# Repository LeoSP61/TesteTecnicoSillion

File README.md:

# TesteTecnicoSillion
Desafio Hardware/Firmware - Sillion

Considerações iniciais: 
O Projeto foi feito seguindo as premissas apresentadas no documento Desafio Hardware/Firmware - Sillion (https://docs.google.com/document/d/1DJPGadSPsPmk1VQU9ZT9On-CVbZ3AcXDxckCV0j4miA/edit).

Como não foram especificadas as características do motor, assumi todo o circuito não consumiria mais que 2A. 

Devido ao prazo curto, não desenvolvi por completo a fonte opcional do exercício 6. Porém, tenho o costume de dimensionar fontes/conversores utilizando a ferramenta WEBENCH POWER DESIGNER da Texas Instruments como auxílio. 
Então entrei com as características necessárias: Conversor Buck (ou buck_boost) entrada 5V a 36V e saída 5V@2A. A partir dos resultados escolhi o circuito que utiliza o CI TPS55288RPMR por ter um footprint reduzido e disponibilidade no mercado. 
O relatório do circuito modelo está anexado no repositório.

Qualquer dúvida, sintam-se a vontade para entrar em contato.

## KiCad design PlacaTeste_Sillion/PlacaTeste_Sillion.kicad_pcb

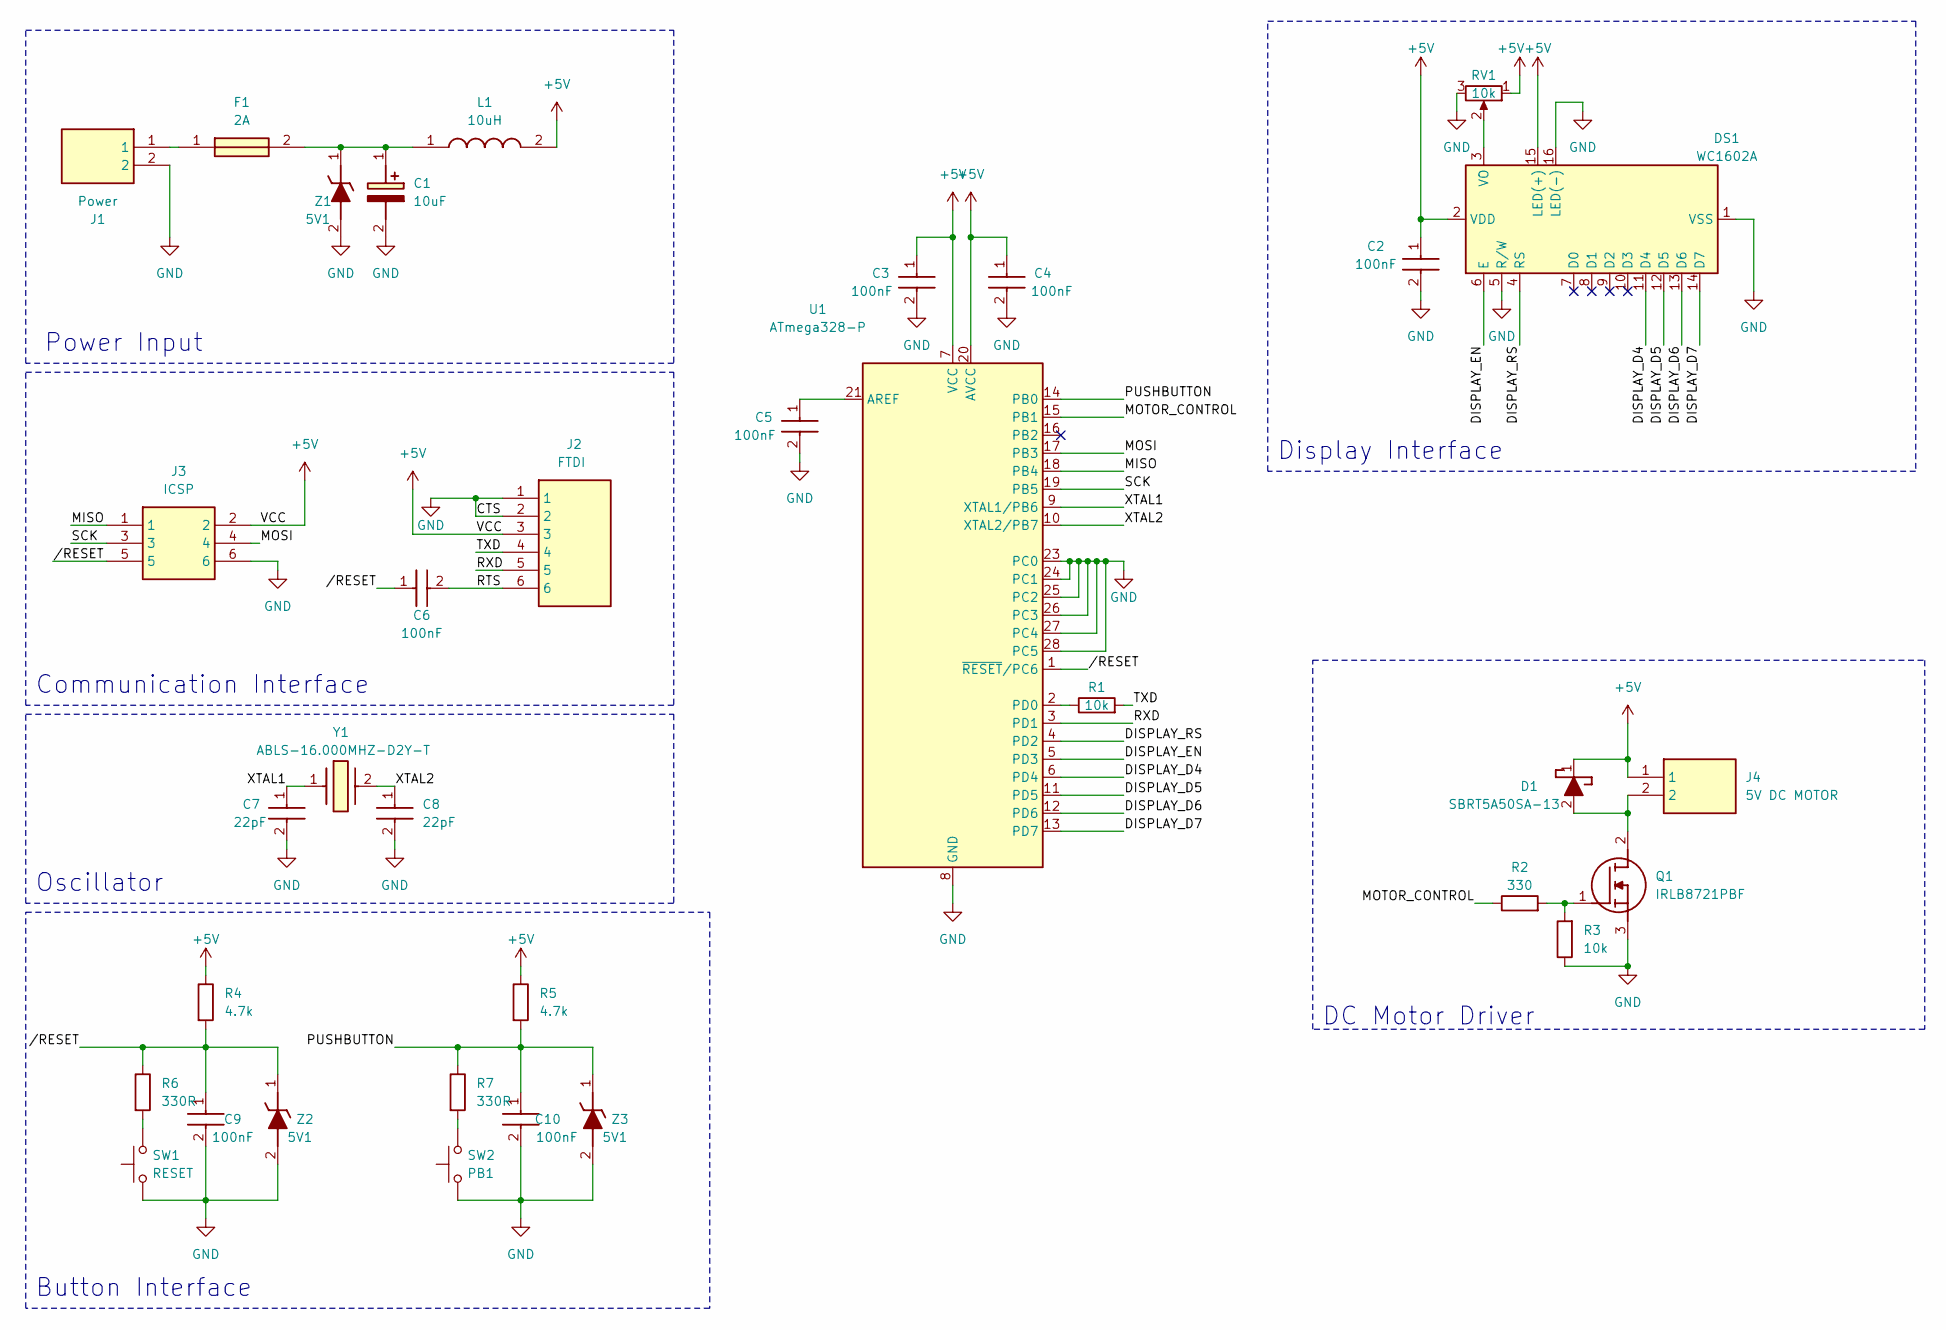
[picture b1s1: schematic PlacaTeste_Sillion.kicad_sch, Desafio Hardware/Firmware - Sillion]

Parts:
C1: 10uF; EEE1AA220WR; Mouser Part Number 667-EEE-FTH100UAR
C2, C3, C4, C5, C6, C9, C10: 100nF; CAPC2012X145N; Mouser Part Number 77-VJ0805Y104MXAMR
C7, C8: 22pF; CAPC2012X94N; Mouser Part Number 581-08055A220FAT2A
D1: SBRT5A50SA-13; DIOM5226X240N; Mouser Part Number 621-SBRT5A50SA-13
DS1: WC1602A
F1: 2A; 39512000000; Mouser Part Number 576-3951200000
J1: Power; 1731721; Mouser Part Number 651-1731721
J2: FTDI; HDRV6W64P0X254_1X6_1524X254X838P; Mouser Part Number 200-HTSW10607TS
J3: ICSP; HDRV6W64P254_2X3_762X508X838P; Manufacturer_Part_Number TSW-103-23-T-D
J4: 5V DC MOTOR; 1731721; Mouser Part Number 651-1731721
L1: 10uH; INDPM4441X120N; Mouser Part Number 652-SRP4012CC-3R3M
Q1: IRLB8721PBF; TO254P483X1016X1994-3P; Mouser Part Number 942-IRLB8721PBF
R1, R3: 10k; R_0805_2012Metric; Manufacturer_Part_Number RP0805BRD0710KL; Mouser Part Number 603-RP0805BRD0710KL
R2: 330; R_0805_2012Metric; Manufacturer_Part_Number SDR10EZPJ331; Mouser Part Number 755-SDR10EZPJ331
R4, R5: 4.7k; R_0805_2012Metric; Manufacturer_Part_Number ERJ-HP6D4701V; Mouser Part Number 667-ERJ-HP6D4701V
R6, R7: 330R; R_0805_2012Metric; Manufacturer_Part_Number SDR10EZPJ331; Mouser Part Number 755-SDR10EZPJ331
RV1: 10k; PVG5A100C03R00; Manufacturer_Part_Number PVG5A100C03R00; Mouser Part Number 81-PVG5A100C03R00
SW1: RESET; TS026643BK260LCRD; Manufacture_Part_Number TS02-66-43-BK-260-LCR-D; Mouser Part Number 179-TS026643BK260LCR
SW2: PB1; TS026643BK260LCRD; Manufacture_Part_Number TS02-66-43-BK-260-LCR-D; Mouser Part Number 179-TS026643BK260LCR
U1: ATmega328-P; DIP-28_W7.62mm; Manufacturer_Part_Number ATMEGA328P-PN; Mouser Part Number 556-ATMEGA328P-PN
Y1: ABLS-16.000MHZ-D2Y-T; ABLS; Mouser Part Number 815-ABLS16MHZD2YT
Z1, Z2, Z3: 5V1; PTZTFTE2551B; Mouser Part Number 755-PTZTFTE255.1B

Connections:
+5V: C2.1, C3.1, C4.1, D1.1 (K), DS1.2 (VDD), DS1.15 (LED(+)), J2.3, J3.2, J4.1, L1.2, R4.1, R5.1, RV1.1, U1.7 (VCC), U1.20 (AVCC)
/DISPLAY_D4: DS1.11 (D4), U1.6 (PD4)
/DISPLAY_D5: DS1.12 (D5), U1.11 (PD5)
/DISPLAY_D6: DS1.13 (D6), U1.12 (PD6)
/DISPLAY_D7: DS1.14 (D7), U1.13 (PD7)
/DISPLAY_EN: DS1.6 (E), U1.5 (PD3)
/DISPLAY_RS: DS1.4 (RS), U1.4 (PD2)
/MISO: J3.1, U1.18 (PB4)
/MOSI: J3.4, U1.17 (PB3)
/MOTOR_CONTROL: R2.1, U1.15 (PB1)
/PUSHBUTTON: C10.1, R5.2, R7.1, U1.14 (PB0), Z3.1 (K)
/RTS: C6.2, J2.6
/RXD: J2.5, U1.3 (PD1)
/SCK: J3.3, U1.19 (PB5)
/TXD: J2.4, R1.2
/XTAL1: C7.1, U1.9 (XTAL1/PB6), Y1.1
/XTAL2: C8.1, U1.10 (XTAL2/PB7), Y1.2
//RESET: C6.1, C9.1, J3.5, R4.2, R6.1, U1.1 (~RESET/PC6), Z2.1 (K)
GND: C1.2 (-), C2.2, C3.2, C4.2, C5.2, C7.2, C8.2, C9.2, C10.2, DS1.1 (VSS), DS1.5 (R/W), DS1.16 (LED(-)), J1.2, J2.1, J2.2, J3.6, Q1.3 (S), R3.1, RV1.3, SW1.1, SW1.2, SW2.1, SW2.2, U1.8 (GND), U1.22 (GND), U1.23 (PC0), U1.24 (PC1), U1.25 (PC2), U1.26 (PC3), U1.27 (PC4), U1.28 (PC5), Z1.2 (A), Z2.2 (A), Z3.2 (A)
unnamed: C1.1 (+), F1.2, L1.1, Z1.1 (K)
unnamed: D1.2 (A), J4.2, Q1.2 (D)
unnamed: DS1.3 (VO), RV1.2
unnamed: F1.1, J1.1
unnamed: Q1.1 (G), R2.2, R3.2
unnamed: R6.2, SW1.3, SW1.4
unnamed: R7.2, SW2.3, SW2.4
unnamed: C5.1, U1.21 (AREF)
unnamed: R1.1, U1.2 (PD0)

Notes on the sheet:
Display Interface
Oscillator
DC Motor Driver
Communication Interface
Button Interface
Power Input

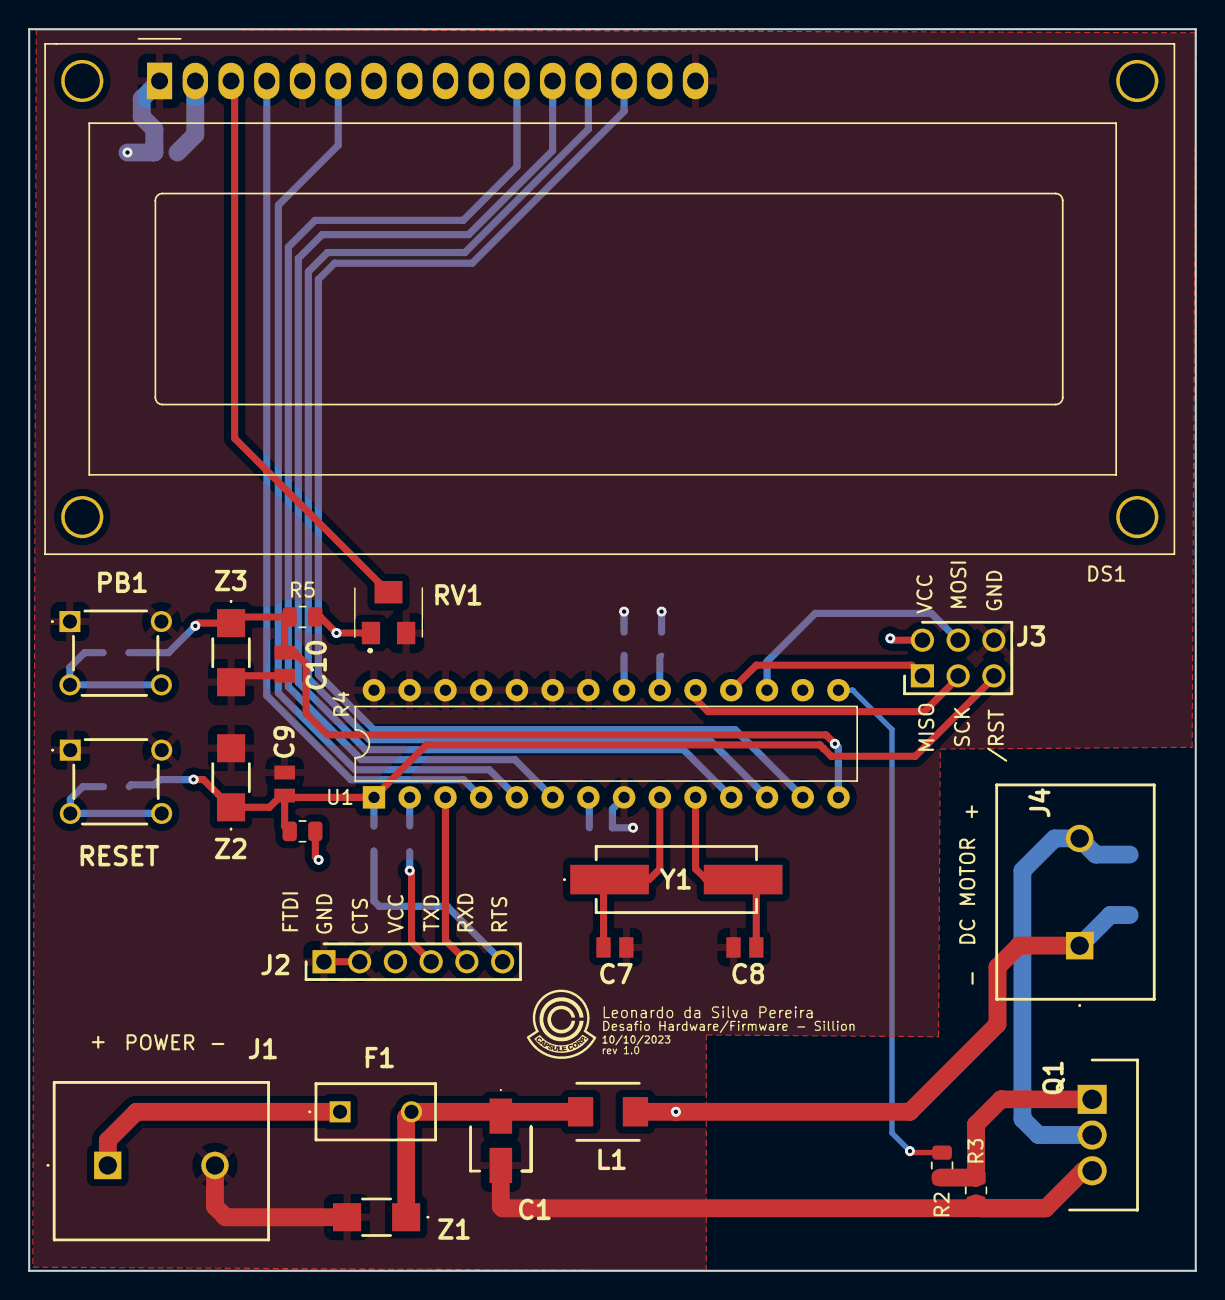
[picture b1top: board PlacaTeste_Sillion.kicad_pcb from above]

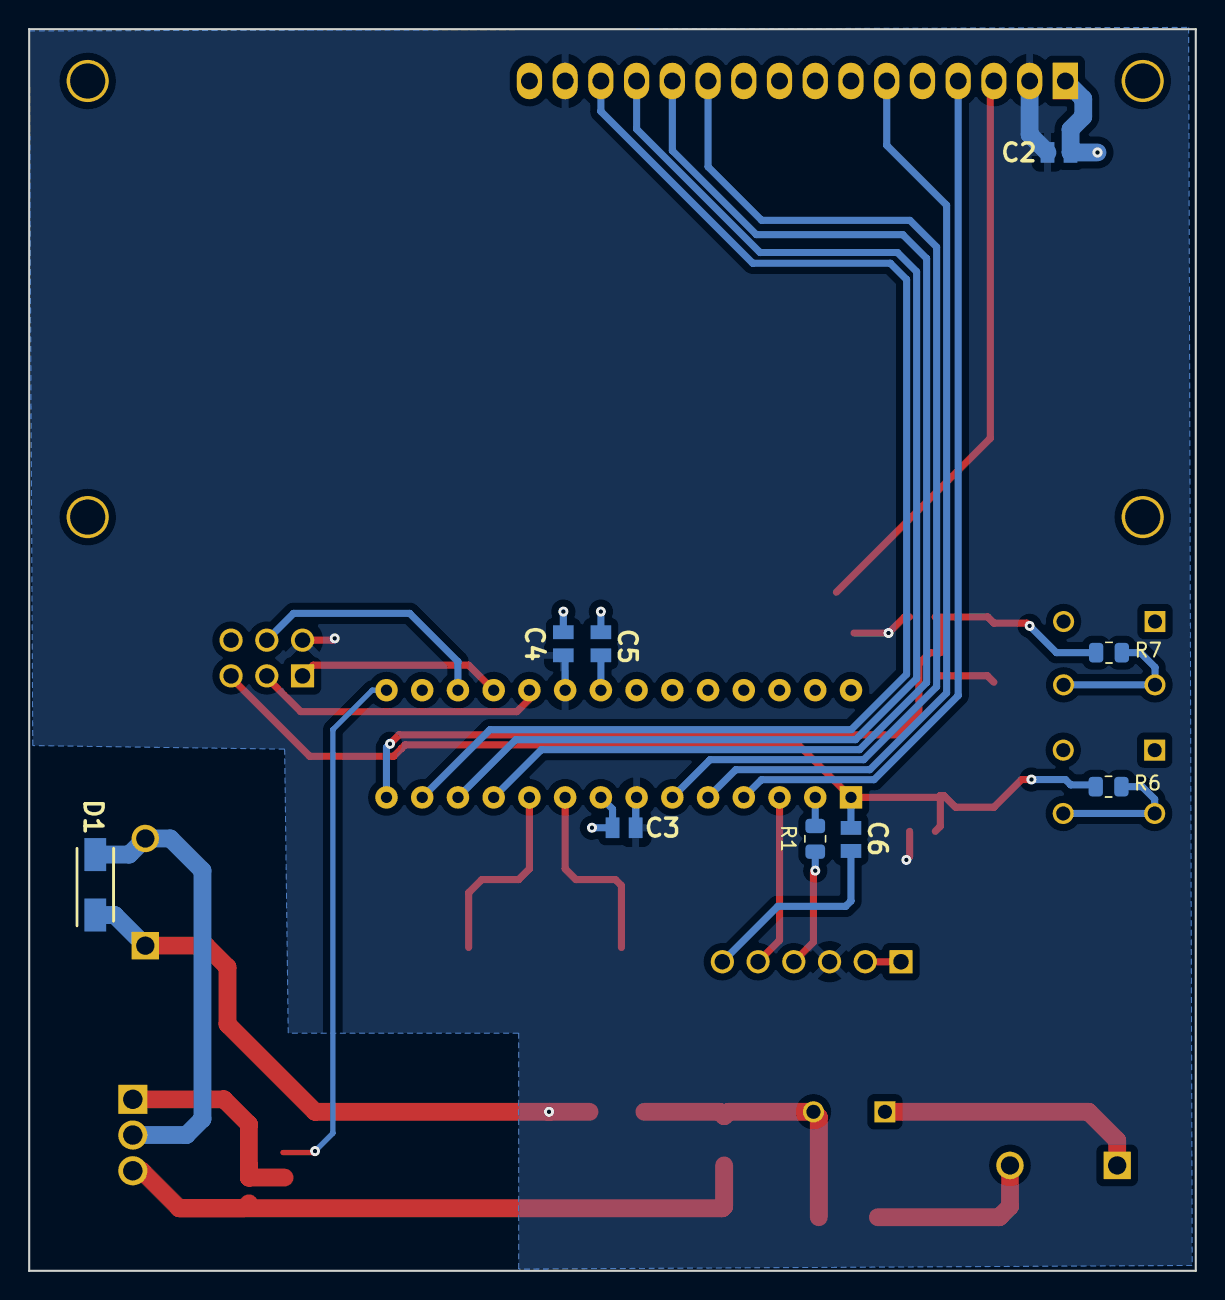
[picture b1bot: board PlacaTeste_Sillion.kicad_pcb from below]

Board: 2 copper layers, 82.9 x 88.3 mm, 34 parts (9 on the bottom side), 28 nets.

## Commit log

2023-10-10 Primeiro commit
